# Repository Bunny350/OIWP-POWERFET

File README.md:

# OIWP-POWERFET

>[!CAUTION]
> This branch contains an abandoned revision of POWERFET. It was initially made in late 2023 and was supposed to be released within early to mid of 2024. Unfortunately I got lazy on it and its development weren't smooth and it didn't released. Because of these reasons, POWERFET G2 (which was supposed to be unveiled in late 2024), was made, will be marked official and is recommended for new designs. Please check the known issues section on why the development is not smooth.

This branch contains the first generation of Oitswilliam Pang POWERFET. You may use it for evaluation and not use it for actual hardware uses.

## Known issues
* The P-channel switch uses 100K resistors to turn off, which is known to have unregulated voltage.
    * *In POWERFET G2 however, it instead uses Zener diode to have regulated voltage.* 
* The component identifiers are not standardized.
    * *In later generations or variants of POWERFET, this is fixed.*

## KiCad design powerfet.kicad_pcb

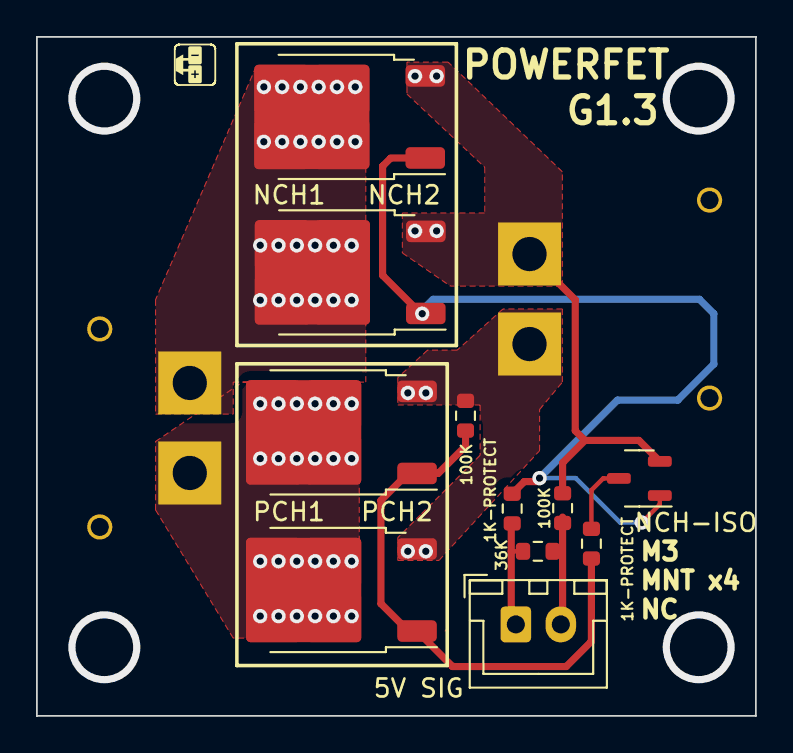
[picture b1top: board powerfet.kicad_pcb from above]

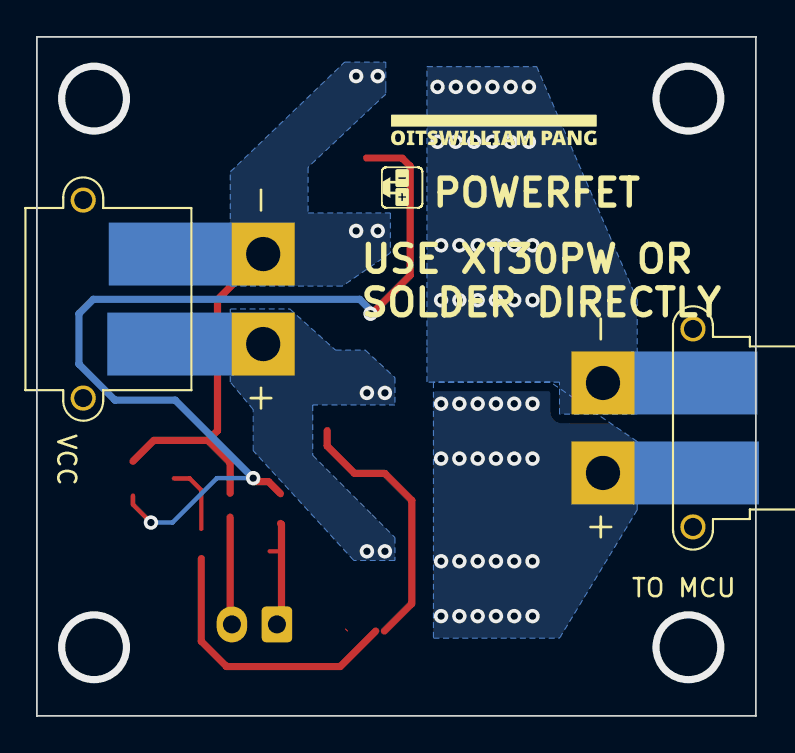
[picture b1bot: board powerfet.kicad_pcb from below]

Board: 2 copper layers, 39.9 x 37.7 mm, 13 parts (2 on the bottom side), 9 nets.

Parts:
1K-PROTECT, 1K-PROTECT#2, 36K, 100K, 100K#2: R_0603_1608Metric
5V SIG: JST_XH_B2B-XH-A_1x02_P2.50mm_Vertical
NCH1, NCH2: TO-252-2
NCH-ISO: SOT-23-3
PCH1, PCH2: TO-252-2
TO MCU: AMASS_XT30PW-F_1x02_P2.50mm_Horizontal
VCC: AMASS_XT30PW-M_1x02_P2.50mm_Horizontal

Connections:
5V+: 1K-PROTECT.2, NCH1.1, NCH2.1, NCH-ISO.1
5V+P: 1K-PROTECT.1, 5V SIG.5V+, 36K.2
5VG: 5V SIG.5VG, 36K.1, 100K.1
5VGD: 1K-PROTECT#2.2, NCH-ISO.3
5VGDA: 1K-PROTECT#2.1, 100K#2.1, PCH1.1, PCH2.1
GND: 100K.2, NCH1.3, NCH2.3, NCH-ISO.2, VCC.1
GND-AFTER: NCH1.2, NCH2.2, TO MCU.1
VCC: 100K#2.2, PCH1.3, PCH2.3, VCC.2
VCC-AFTER: PCH1.2, PCH2.2, TO MCU.2

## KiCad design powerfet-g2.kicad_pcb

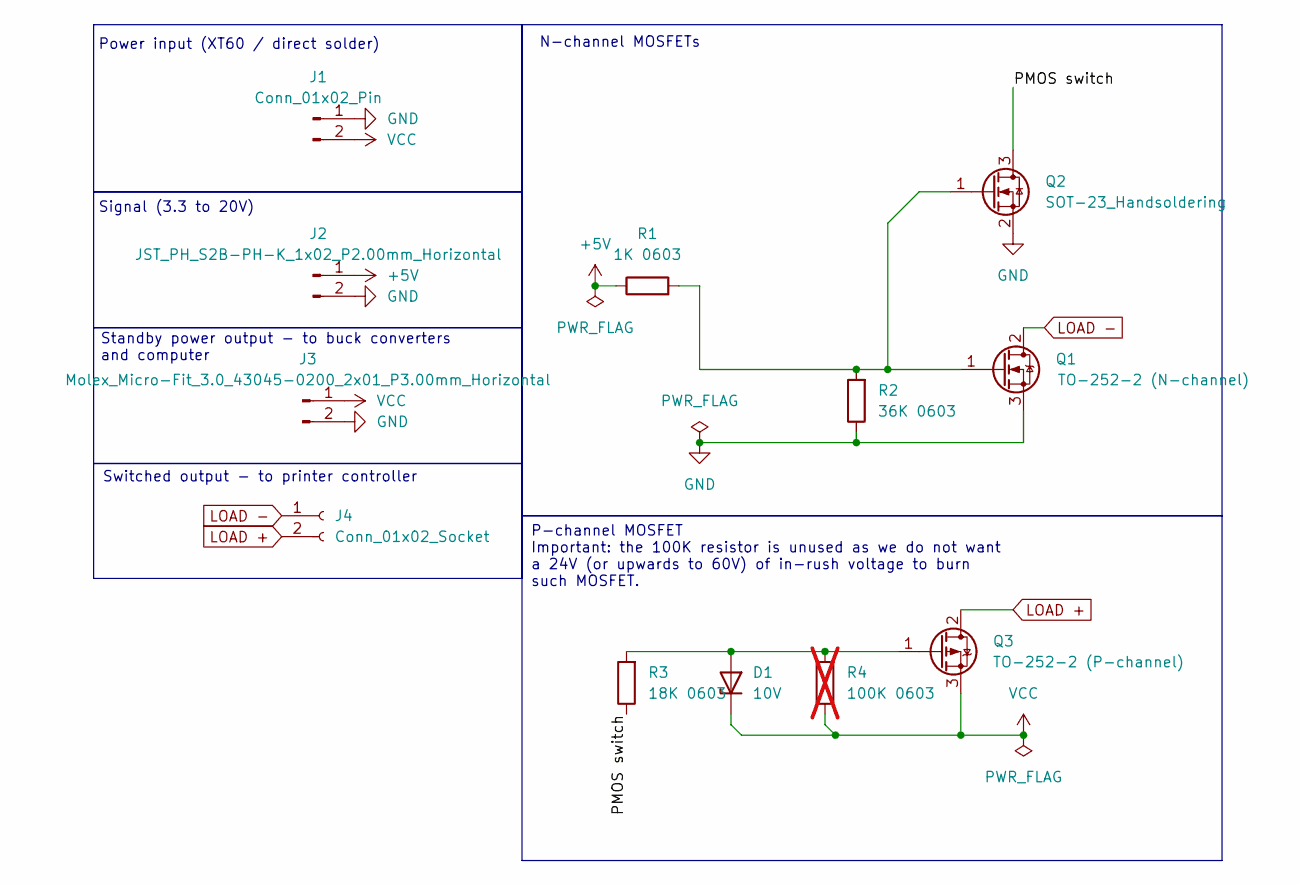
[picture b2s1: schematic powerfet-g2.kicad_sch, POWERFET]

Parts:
D1: 10V; D_SOD-123
J1: Conn_01x02_Pin; AMASS_XT30PW-M_1x02_P2.50mm_Horizontal
J2: JST_PH_S2B-PH-K_1x02_P2.00mm_Horizontal
J3: Molex_Micro-Fit_3.0_43045-0200_2x01_P3.00mm_Horiz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; Molex_Micro-Fit_3.0_43045-0200_2x01_P3.00mm_Horizontal
J4: Conn_01x02_Socket; AMASS_XT30PW-F_1x02_P2.50mm_Horizontal
Q1: TO-252-2 (N-channel); TO-252-2
Q2: SOT-23_Handsoldering
Q3: TO-252-2 (P-channel); TO-252-2
R1: 1K 0603; R_0805_2012Metric
R2: 36K 0603; R_0805_2012Metric
R3: 18K 0603; R_0805_2012Metric
R4: 100K 0603; R_0805_2012Metric; not fitted

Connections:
+5V: J2.1, R1.1
/PMOS switch: Q2.3 (D), R3.1
GND: J1.1, J2.2, J3.2, Q1.3 (S), Q2.2 (S), R2.1
LOAD +: J4.2, Q3.2 (D)
LOAD -: J4.1, Q1.2 (D)
unnamed: D1.2 (A), Q3.1 (G), R3.2, R4.2
unnamed: Q1.1 (G), Q2.1 (G), R1.2, R2.2
VCC: D1.1 (K), J1.2, J3.1, Q3.3 (S), R4.1

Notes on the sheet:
P-channel MOSFET Important: the 100K resistor is unused as we do not want a 24V (or upwards to 60V) of in-rush voltage to burn such MOSFET.
Power input (XT60 / direct solder)
Standby power output - to buck converters and computer
N-channel MOSFETs
Signal (3.3 to 20V)
Switched output - to printer controller

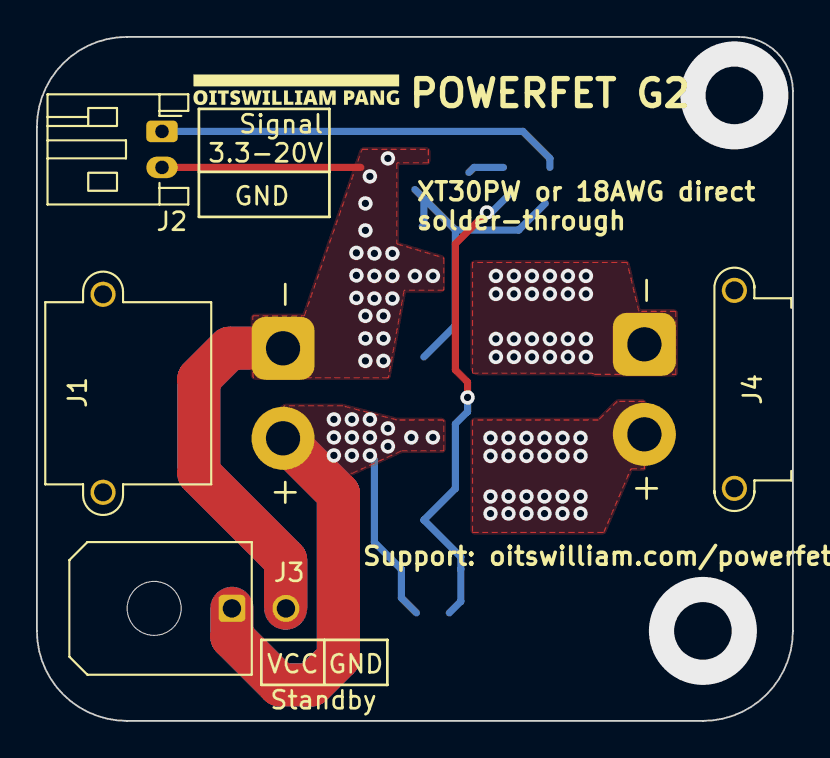
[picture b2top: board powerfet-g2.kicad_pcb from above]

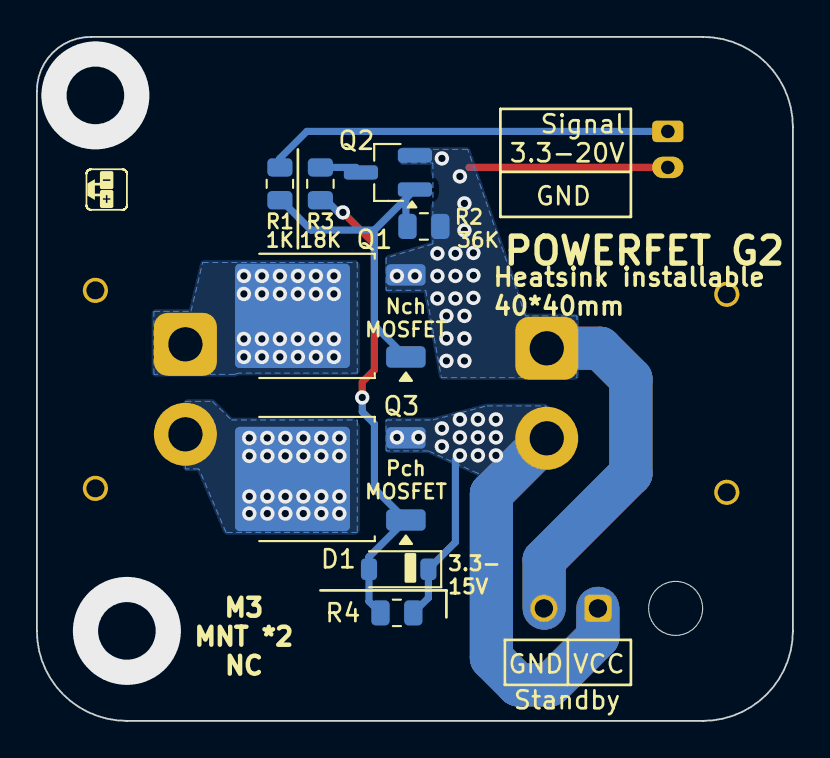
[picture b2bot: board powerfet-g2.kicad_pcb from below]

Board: 2 copper layers, 42.0 x 38.0 mm, 12 parts (8 on the bottom side), 8 nets.
